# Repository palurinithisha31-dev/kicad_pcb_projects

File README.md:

# kicad_pcb_projects
pcb projects

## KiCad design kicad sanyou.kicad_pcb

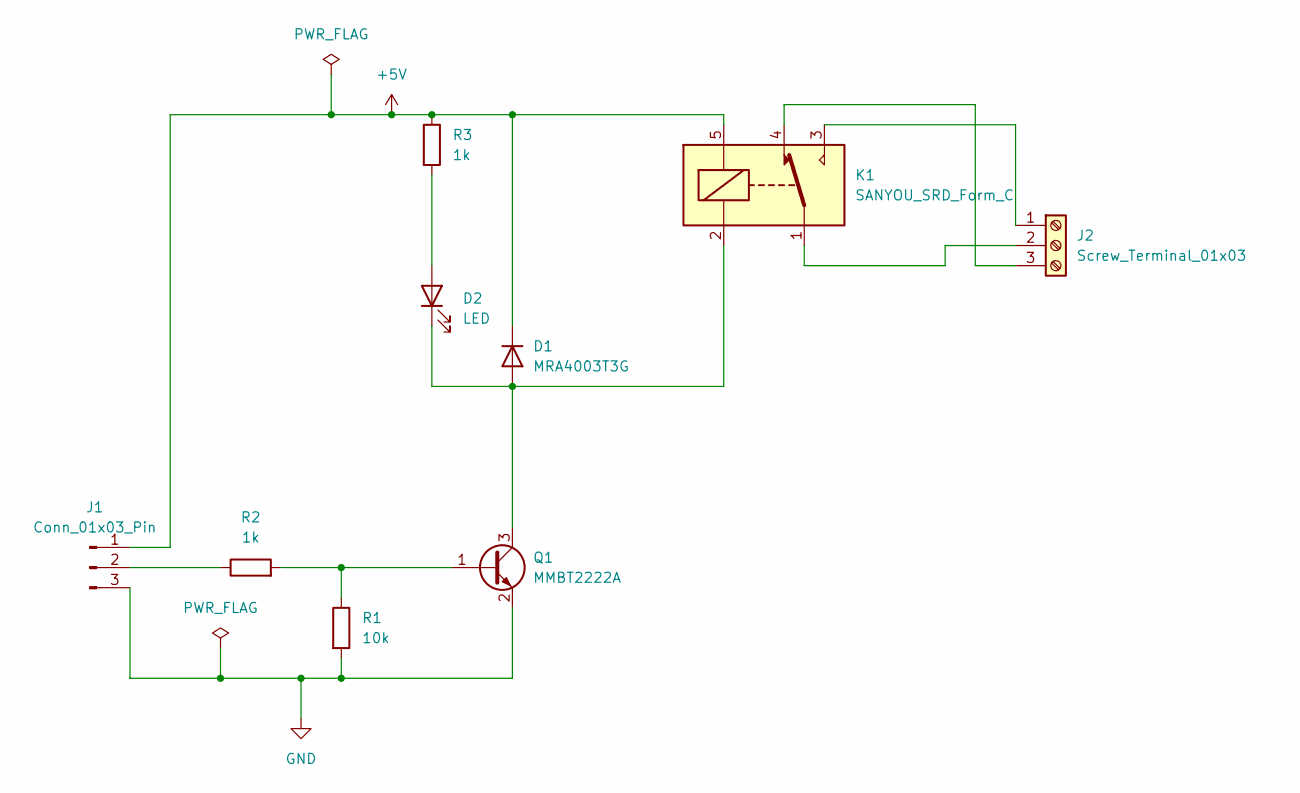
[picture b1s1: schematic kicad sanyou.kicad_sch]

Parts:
D1: MRA4003T3G; D_SMA
D2: LED; LED_D3.0mm_Clear
J1: Conn_01x03_Pin; PhoenixContact_GMSTBA_2,5_3-G-7,62_1x03_P7.62mm_Horizontal
J2: Screw_Terminal_01x03; TerminalBlock_MaiXu_MX126-5.0-03P_1x03_P5.00mm
K1: SANYOU_SRD_Form_C; Relay_SPDT_SANYOU_SRD_Series_Form_C
Q1: MMBT2222A; SOT-23
R1: 10k; R_Axial_DIN0204_L3.6mm_D1.6mm_P7.62mm_Horizontal
R2, R3: 1k; R_Axial_DIN0204_L3.6mm_D1.6mm_P7.62mm_Horizontal

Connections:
+5V: D1.1 (K), J1.1, K1.5, R3.1
GND: J1.3, Q1.2 (E), R1.2
unnamed: D1.2 (A), D2.1 (K), K1.2, Q1.3 (C)
unnamed: D2.2 (A), R3.2
unnamed: J1.2, R2.1
unnamed: J2.1, K1.3
unnamed: J2.2, K1.1
unnamed: J2.3, K1.4
unnamed: Q1.1 (B), R1.1, R2.2

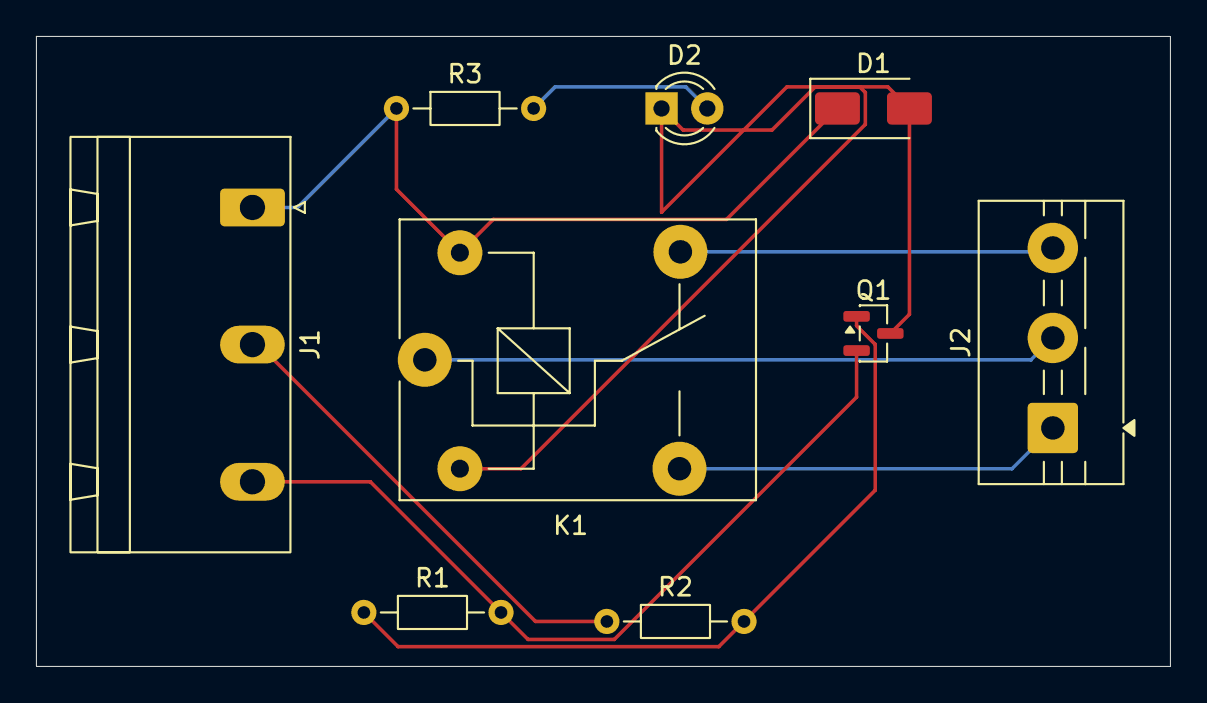
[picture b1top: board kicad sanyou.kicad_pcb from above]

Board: 2 copper layers, 63.0 x 35.0 mm, 9 parts (0 on the bottom side), 9 nets.
